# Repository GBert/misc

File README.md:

OpenWrt railroad files
======================

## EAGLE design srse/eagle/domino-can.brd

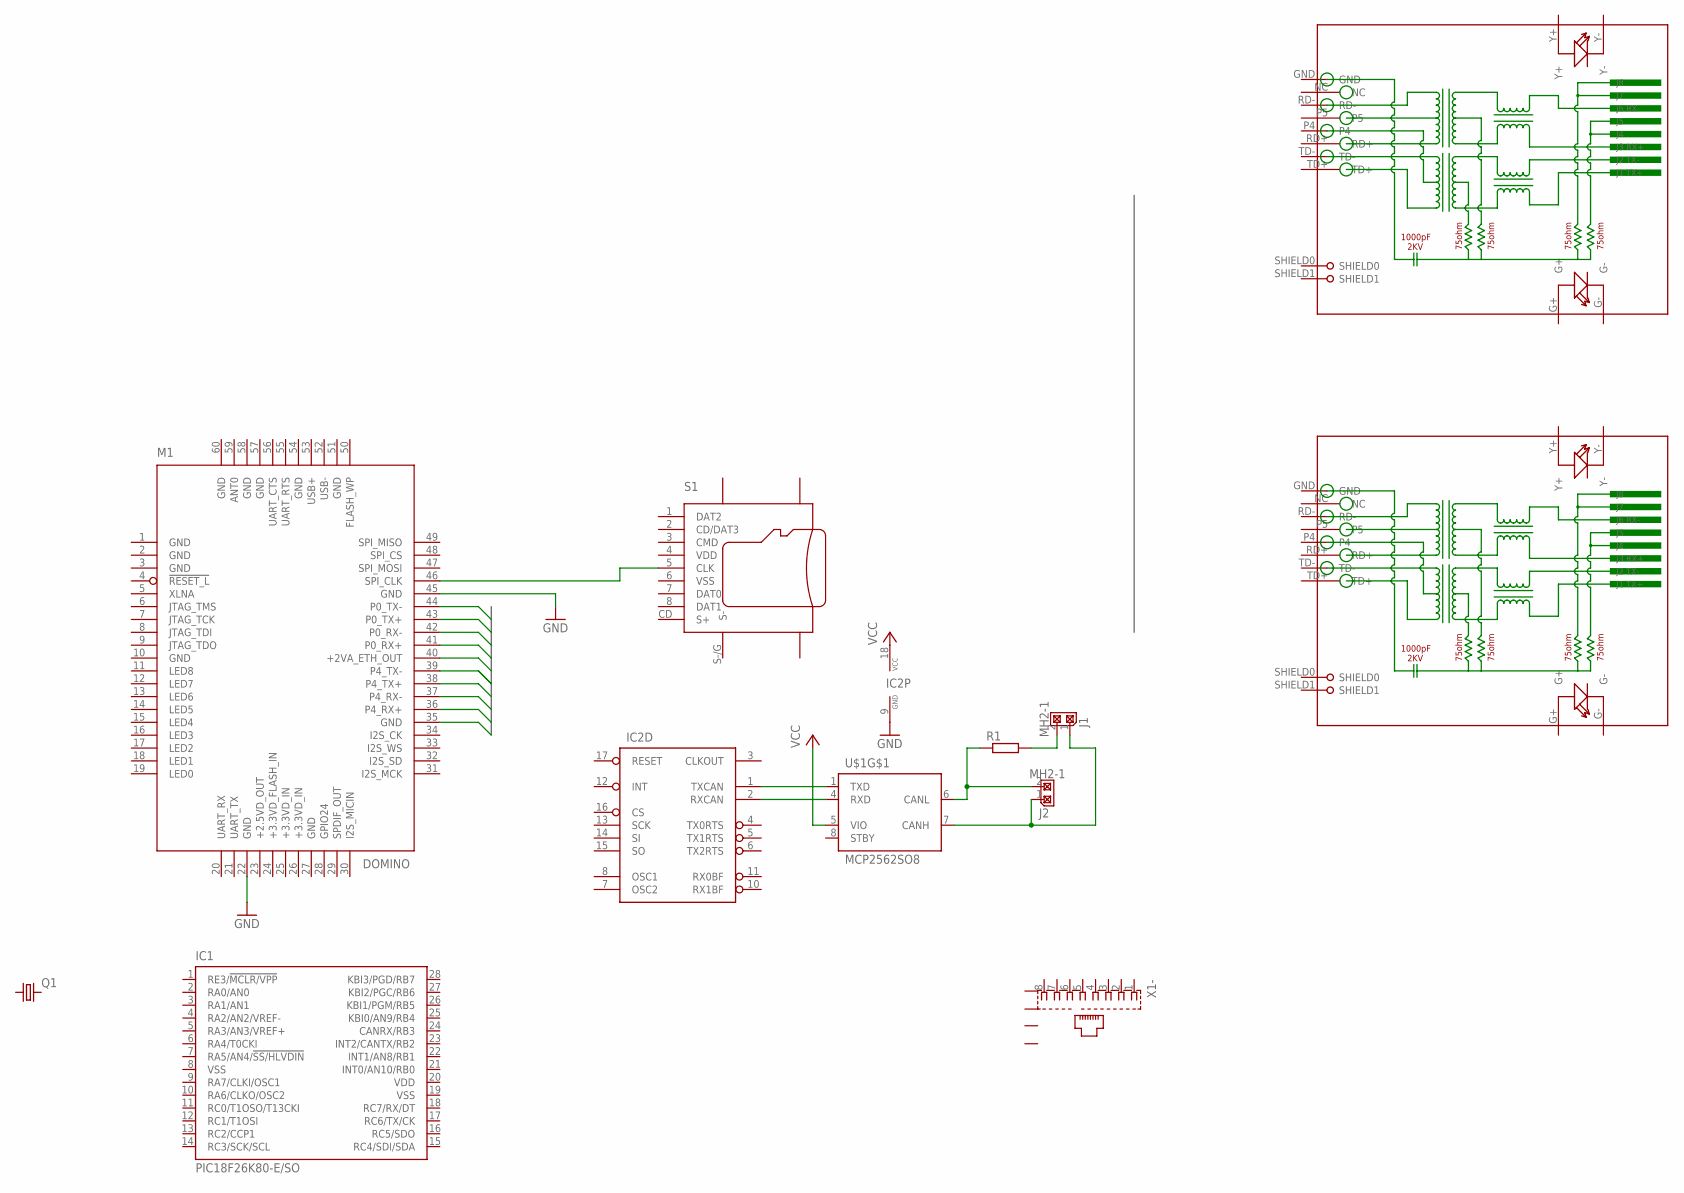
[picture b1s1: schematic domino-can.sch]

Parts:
IC1: PIC18F26K80-E/SO; SO28W
IC2: MCP2515SO; SO-18W
J1, J2: MH2-1; MH2-1-0.1
M1: DOMINO
Q1: CRYSTALHC49S; HC49/S
R1: R-EU_R1206; R1206
RJ1, RJ2: HR911105A
S1: MICRO-SD; SD-007
U$1: MCP2562SO8; SO08
X1: RJ45

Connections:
+2VA_ETH_OUT: M1.40 (+2VA_ETH_OUT)
+3.3VD_FLASH_IN: M1.24 (+3.3VD_FLASH_IN)
+3.3VD_IN: M1.25 (+3.3VD_IN), M1.26 (+3.3VD_IN)
G: S1.G$1 (G), S1.G$2 (G), S1.G$3 (G)
GND: IC2.9 (GND), M1.1 (GND), M1.2 (GND), M1.3 (GND), M1.10 (GND), M1.22 (GND), M1.27 (GND), M1.45 (GND), M1.51 (GND), M1.54 (GND), M1.57 (GND), M1.58 (GND), M1.60 (GND), U$1.2 (GND)
GND@10: M1.35 (GND)
unnamed: M1.46 (SPI_CLK), S1.5 (CLK)
unnamed: IC2.1 (TXCAN), U$1.1 (TXD)
unnamed: IC2.2 (RXCAN), U$1.4 (RXD)
unnamed: J2.2, R1.1, U$1.6 (CANL)
unnamed: J1.1, J2.1, U$1.7 (CANH)
unnamed: J1.2, R1.2
S-: S1.S-/G (S-)
VCC: IC2.18 (VCC), U$1.3 (VCC), U$1.5 (VIO)
VDD: IC1.20 (VDD), S1.4 (VDD)
VSS: IC1.8 (VSS), IC1.19 (VSS), S1.6 (VSS)

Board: 2 copper layers, 12 parts (1 on the bottom side), 12 nets, no tracks yet.

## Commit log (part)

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2021-03-24 change icon
2021-03-24 bump revision
2021-03-28 new version from Teddy
2021-03-28 new version bye Rainer Mueller
2021-04-03 fix compiling
2021-04-04 add WebServer/ResponseCsv.cpp
2021-04-04 add changes
2021-04-11 add actual TODO by Teddy
2021-04-16 reflect new version
2021-04-19 add missing files
2021-04-19 Update Makefile
2021-04-19 more generic makefile
2021-04-26 fix missing files
2021-04-30 fix reading magnet data
2021-04-30 fix also here the double freeing
2021-04-30 synchronize between can2udp and z21emu
2021-04-30 synchronize between can2udp and z21emu - 32 function tokens
2021-05-01 new version from Teddy - prepare for multiple loco controls (no new functionality)
2021-05-02 new version from Teddy - fix release of loco list
2021-05-02 update Makefile to new version
2021-05-04 calm down valgrind
2021-05-06 work again on mfx link
2021-05-06 new version of mfx-link
2021-05-06 smaller pics
2021-05-07 add picture where the cirrent sense transfprmer should be connected
2021-05-10 first try at JLCPCB
2021-05-11 fixed rotation / U3 still unclear
2021-05-11 some minimal silkscreen corrections
2021-05-11 P50x changes by Teddy
2021-05-12 new version by Teddy - using CAN responses
2021-05-12 fix U3
2021-05-12 only U1SM fiffers in orientation now
2021-05-12 increment version number to force update
2021-05-13 addded Changelog in readme
2021-05-14 add mfx decoding by Rainer
2021-05-14 fix compiler warning
2021-05-14 updated R17 against GND
2021-05-15 new MS2 ID 0x0033
2021-05-15 we need this file
2021-05-15 Improve viewport - by Teddy
2021-05-16 new version by Teddy
2021-05-18 fix getting F16-F31 from MS2 by Teddy
2021-05-20 new version from Teddy - add Drag&Drop
2021-05-21 new version from Teddy - more Drag&Drop work
2021-05-21 use 16ms timeout to cut off H-Bridge
2021-05-21 add some comments
2021-05-21 prepare ADC interrupt
2021-05-21 Fix pre and post scaler value
2021-05-21 ADC wip
2021-05-21 new version from Teddy - more Drag&Drop
2021-05-23 new production files for JLCPCB
2021-05-23 add tables
2021-05-24 new version from Teddy - allow shift&ctrl keys to rotate/move
2021-05-24 add Reichelt BOM
2021-05-24 add BOM - wip
2021-05-24 BOM - wip
2021-05-25 add picture again
2021-05-25 beautify drawing
2021-05-26 ADC - wip
2021-05-27 fix GND plane for IO
2021-05-27 add actual pdf
2021-05-28 use a slightly higher ADC speed
2021-05-28 fix LCSC part number for 22 Ohm resistor
2021-05-29 use different ADC properties
2021-05-29 add +18V ADC input
2021-05-30 allign text
2021-05-30 aad more data
2021-06-01 add a comment
2021-06-04 add some modiing pictures for early revisions
2021-06-04 add some wiring pictures
2021-06-04 add some hints
2021-06-04 we don't use cs2.exe
2021-06-04 use different pic sizes correctly
2021-06-10 stm32-slcan:adapted to the latest library, cleaning up a possibly corrupted package read from a uart
2021-06-11 wip - probably the most complicated multichannel ADC ever ...
2021-06-11 minimize SENSE variation
2021-06-11 us bit fields
2021-06-14 gcc11 fix by Teddy
2021-06-17 add IRQ latency hint
2021-06-19 Fix P50x booster on/off by Teddy
2021-06-20 make some use of Timer0
2021-06-21 add E146781 using
2021-06-21 use table
2021-06-21 fix doc
2021-06-21 P82B715 not needed
2021-06-24 reflect new version in makefile
2021-06-25 new version from Teddy - reorganize protocol implementation
2021-06-28 add ESU files from Teddy
2021-06-28 add missing header
2021-07-02 add new schematic pdf
2021-07-02 xc8 firmware by Martin Krause
2021-07-04 some modifictaions from Martin Krause
2021-07-20 change resistors for voltage measurement as suggested by Martin K.
2021-07-20 add voltage measurement picture
2021-07-20 add voltage measurement picture - soldered
2021-07-20 a little bit alrger
2021-07-23 add missing file
2021-08-20 add XpressNet device (RS485 9N1) - wip
2021-08-25 fix ASCII schematic and UBAUD calculation
2021-08-25 add back srse2 files
2021-08-25 prepare XpressNet
2021-08-27 testing simple RS485 device with CP2104
2021-08-27 adress and data bits look better now, but there is a gap between address and first data byte
2021-08-27 add some remarks regarding CP2104 with RS485
2021-08-28 use option interface and be more verbose on failure
2021-08-28 try to use standard termios to set custom baudrate
2021-08-30 some messages are only one byte - don't need to waste time swichting from address to data mode
2021-09-11 reduce parity changes to speed up
2021-09-11 more XPN testing code - wip
2021-09-12 use Access ram - more XpressNet testing
2021-09-14 deocde the XPN init - wip
2021-09-14 simplify a little bit
2021-09-14 now in stage loco info
2021-09-14 show more data received from throttle
2021-09-14 loco settings seems to work but it's getting ugly ...
2021-09-14 easier debugging
2021-09-15 track on/off - wip
2021-09-15 more comments
2021-09-15 save power on/off
2021-09-16 power state handling - wip
2021-09-17 CAN power change will be send to XpressNet
2021-09-17 XPN power change to CAN - wip (something is wrong here)
2021-09-17 hex files bcak
2021-09-17 hex files back
2021-09-19 XPN power change to CAN fix
2021-09-19 reuse CAN event mechanismen for XpressNet -> CAN/UART
2021-10-24 add STM32 SLCAN back
2021-11-04 change U_in calc for 10k/1k8 divider
2021-11-24 partly SMD PCB
2021-11-26 add small pic
2021-12-01 make V1.6 for JLCPCB Assemly Service
2021-12-05 for Microchip forum
2021-12-11 add hint
2021-12-11 new JLCPCB assembly version V1.7
2021-12-21 add SMD JLCPCB V1.7 picture
2022-01-05 fix LCSC part numbers
2022-01-05 move CPL file
2022-01-06 why not to connect Railground to S88 ground
2022-01-17 fixing iTrain channel mechnismn
2022-01-17 update hex file
2022-01-18 backup 1.12 version
2022-02-18 add some 60174 pics
2022-02-27 add actual schematic pdf
2022-02-27 add Power supply hint
2022-02-28 add actual schamitc pdf
2022-03-08 add s88 pic
2022-04-12 test OpenScad
2022-06-16 add HEX file
2022-06-18 fix Makefile
2022-10-21 add DCDC converter - wip
2022-10-21 move components to satisfy DCDC requirements
2022-10-31 add pics
2022-11-07 new SRSEII JLCPCB production files Version 1.8
2022-11-08 add 3D pic of V1.8
2022-11-08 add small version of picture
2022-11-20 add new production ZIP
2022-12-08 remove old 3V3 DCDC
2022-12-21 keep HEX file
2022-12-21 new date
2023-01-22 fix schematic - no existing GND interconnect
2023-02-09 fix PIC placing
2023-02-09 fix PIC placing - back to 270 orientation
2023-02-09 add Gerber files
2023-02-09 move power supply text a little bit
2023-02-12 add universal CAN mini adpater
2023-02-15 add some LinkS88 pictures
2023-02-23 add some pics
2023-02-24 fix pin header description and use larger resistors
2023-02-24 add MS1 Slave / Pin 5 Vcc
2023-02-24 rename JP2 to MS1 Master
2023-02-25 add some MS1 extension pics
2023-02-25 add Chagelog
2023-02-26 move some description on the silkscreen
2023-02-26 add CAN Power description pic
2023-02-26 add LinkS88 with SRSEII pic
2023-02-27 Hinweis auf die Bauteil-Quellen
2023-03-03 add some GND vias
2023-03-06 add Pi Pico test programm
2023-03-15 add actual schematic
2023-03-16 add some conditional compiling for XPN and CAN LED
2023-03-16 new version 1.14 with power status on D2
2023-03-16 Update Changelog.md
    Add missing Version Description
2023-03-16 Update Changelog.md
    Fix typo
2023-03-18 use the NO_CAN_LED switch correctly
2023-03-29 fix part placement
2023-03-29 fix part placement - now
2023-04-17 add german translation doc
2023-04-20 switch to Kicad 6.0 and add schematic pdf
2023-09-18 add production file with 2mm pin header
2023-09-23 add setup picture with Pi CAN Hat and LinkS88
2023-11-22 replace 18uH with 15uH - JLCPCB doesn't have Sumida 18uH anymore
2023-11-22 JLCPCB is complaining about missing R13 in BOM
2023-11-22 change LCSC ordering number for L100 15uH
2023-12-01 save the outcomes here
2023-12-01 some basic stuff
2023-12-03 do the decompress as well
2023-12-03 get the filters test
2023-12-10 type filter for ports
2023-12-22 use functions
2023-12-22 use input option
2023-12-22 print ports or filters optional
2023-12-22 use f-string for printing
2023-12-22 sort output
2023-12-22 sort naturally
2023-12-22 sort list as well
2024-03-06 fix S88 ID
2024-03-06 add V1.1 firmware
2024-03-08 fix formatting an Version
2024-03-08 set ID to LinkS88 id
2024-03-09 prepare 0x22 S88
2024-03-09 increase version
2024-03-10 add eeprom routines
2024-03-11 make Device ID independent from HW ID
2024-03-11 fix event ID handling
2024-03-11 add HEX files
2024-03-11 chech Device ID on 0x22 Event Request
2024-03-24 update to KiCad 7.0 - wip
2024-03-26 use 18V symbol instead of 24V
2024-03-26 reorganize schematic
2024-04-11 git rid off warning
2024-04-13 add Omega2 sockets
2024-04-13 fix ERC/DRC errors and warnings / fix bom and placements
2024-04-13 fix local library issue
2024-04-13 switch 18pF caps from 0805 to 0603 for JLCPCB basic parts
2024-04-13 more cutting costs
2024-04-13 smaller fixes - mainly silkscreen
2024-04-13 isolate I2C
2024-04-16 15uH isn't available at JLCPCB - use 18uH instead
2024-04-29 add actual production file
2024-08-22 add pics here
2024-10-13 fix indent
2024-10-13 new version v1.15
2024-10-13 add Martins overflow avoidance
2024-11-25 various changes form M. Krause
2025-01-04 add v1.16 firmware
2025-01-04 new version 1.27
2025-01-04 change 2mm pin socket
2025-01-04 change 2mm pin socket - now
2025-01-17 add pictures here
2025-01-17 add missing pics
2025-12-13 small changes
2025-12-13 add new inlay
2026-01-08 make inlay height vaiable
2026-01-11 fix typo and add cd
2026-01-15 Inlay 2 update and picture
2026-01-15 small size pic of inlay
2026-01-15 move pictures to own dir
